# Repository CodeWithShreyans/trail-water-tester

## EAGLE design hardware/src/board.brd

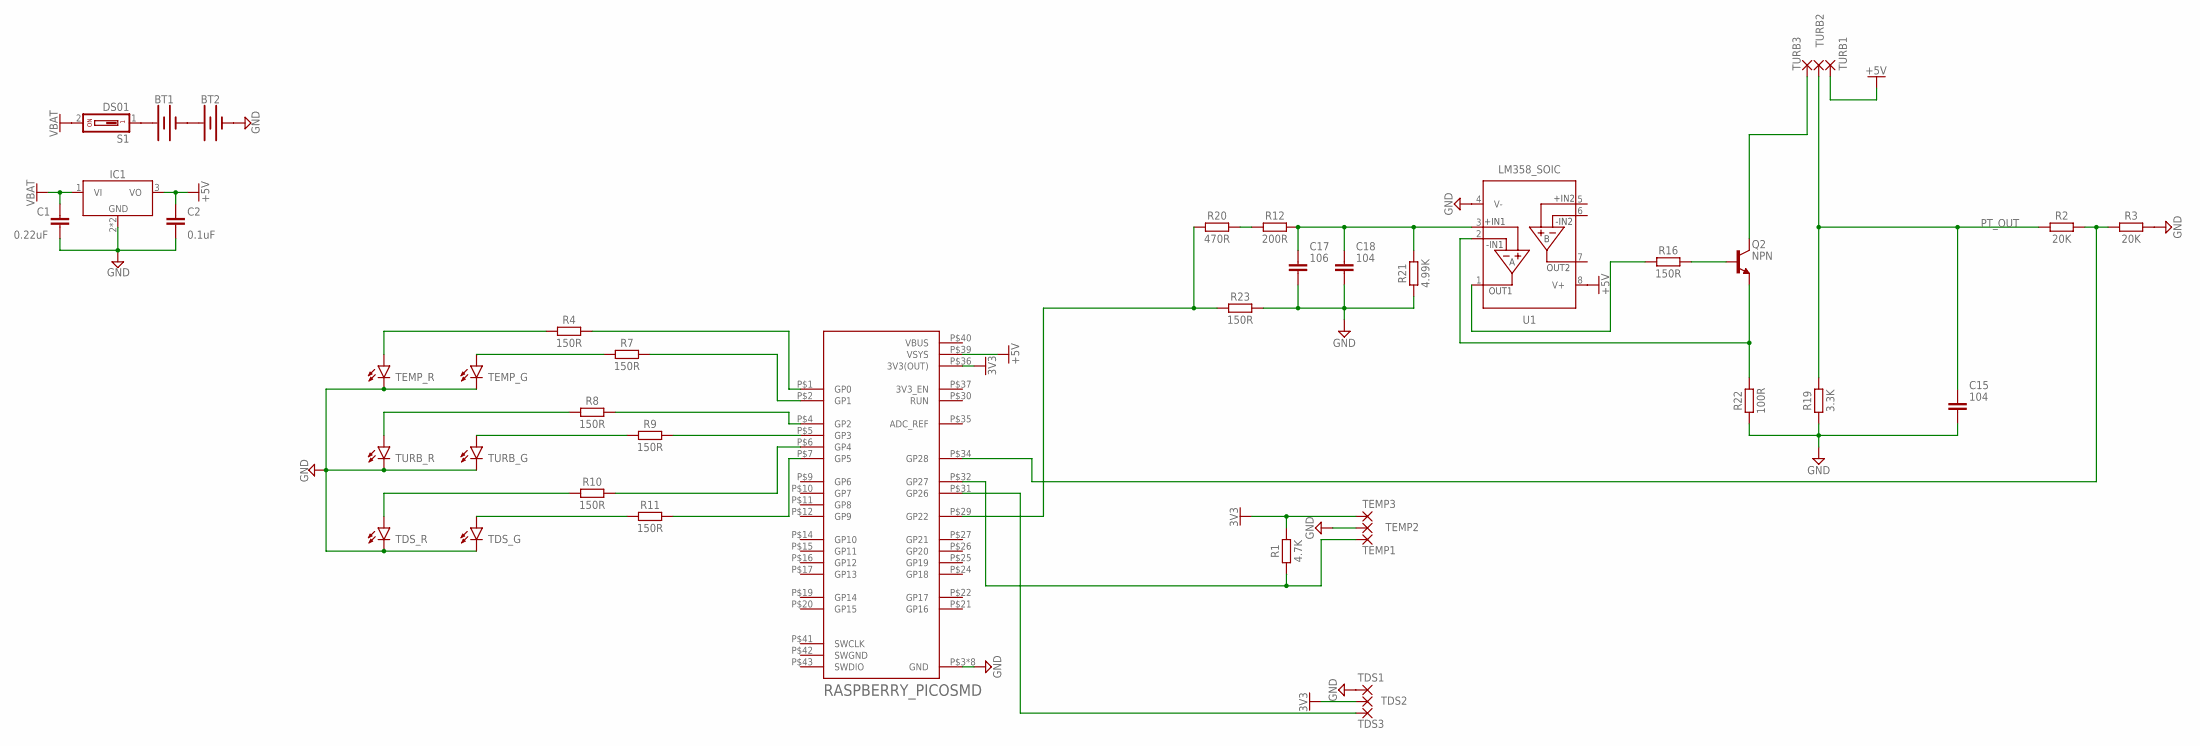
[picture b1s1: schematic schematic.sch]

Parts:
BT1, BT2: BATTERY-20MM_SMD_4LEGS; BATTCON_20MM_4LEGS
C1: 0.22uF; CAPC1608X85
C2: 0.1uF; CAPC1608X85
C15, C18: 104; CAPC1005X60
C17: 106; CAPC1005X60
IC1: LM7805_SOT223; SOT230P700X170-4
Q2: NPN; SOT95P237X112-3N
R1: 4.7K; RESC1005X40
R2, R3: 20K; RESC1005X40
R4, R7, R8, R9, R10, R11, R16, R23: 150R; RESC1005X40
R12: 200R; RESC1005X40
R19: 3.3K; RESC1005X40
R20: 470R; RESC1005X40
R21: 4.99K; RESC1608X60
R22: 100R; RESC1005X40
S1: DS01; DS-01
TDS1, TDS2, TDS3: SMD5; SMD2,54-5,08
TDS_G: CHIP-ROUND-G_0805; LEDC2012X105N_RND-G
TDS_R: CHIP-ROUND-R_0805; LEDC2012X105N_RND-R
TEMP1, TEMP2, TEMP3: SMD5; SMD2,54-5,08
TEMP_G: CHIP-ROUND-G_0805; LEDC2012X105N_RND-G
TEMP_R: CHIP-ROUND-R_0805; LEDC2012X105N_RND-R
TURB1, TURB2, TURB3: SMD5; SMD2,54-5,08
TURB_G: CHIP-ROUND-G_0805; LEDC2012X105N_RND-G
TURB_R: CHIP-ROUND-R_0805; LEDC2012X105N_RND-R
U1: LM358_SOIC; SOIC127P600X175-8N
U2: RASPBERRY_PICOSMD; PICO-PKG-SMD

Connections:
3V3: R1.2, TDS2.1, TEMP3.1, U2.P$36 (3V3(OUT))
+5V: C2.1, IC1.3 (VO), TURB1.1, U1.8 (V+), U2.P$39 (VSYS)
GND: BT2.NEGATIVE (-), C1.2, C2.2, C15.2, C17.2, C18.2, IC1.2 (GND), IC1.4 (GND), R3.2, R19.1, R21.1, R22.1, R23.2, TDS1.1, TDS_G.C, TDS_R.C, TEMP2.1, TEMP_G.C, TEMP_R.C, TURB_G.C, TURB_R.C, U1.4 (V-), U2.P$3 (GND), U2.P$8 (GND), U2.P$13 (GND), U2.P$18 (GND), U2.P$23 (GND), U2.P$28 (GND), U2.P$33 (GND), U2.P$38 (GND)
unnamed: R8.2, U2.P$4 (GP2)
unnamed: R9.2, U2.P$5 (GP3)
unnamed: R1.1, TEMP1.1, U2.P$32 (GP27)
unnamed: R20.1, R23.1, U2.P$29 (GP22)
unnamed: R2.2, R3.1, U2.P$34 (GP28)
unnamed: TDS3.1, U2.P$31 (GP26)
unnamed: R4.1, TEMP_R.A
unnamed: R7.1, TEMP_G.A
unnamed: R8.1, TURB_R.A
unnamed: R9.1, TURB_G.A
unnamed: R11.1, TDS_G.A
unnamed: BT1.NEGATIVE (-), BT2.POSITIVE@1 (+), BT2.POSITIVE@2 (+), BT2.POSITIVE@3 (+), BT2.POSITIVE@4 (+)
unnamed: R11.2, U2.P$7 (GP5)
unnamed: R10.2, U2.P$6 (GP4)
unnamed: BT1.POSITIVE@1 (+), BT1.POSITIVE@2 (+), BT1.POSITIVE@3 (+), BT1.POSITIVE@4 (+), S1.1
unnamed: R4.2, U2.P$1 (GP0)
unnamed: R7.2, U2.P$2 (GP1)
unnamed: R10.1, TDS_R.A
unnamed: R12.1, R20.2
unnamed: C17.1, C18.1, R12.2, R21.2, U1.3 (+IN1)
unnamed: R16.1, U1.1 (OUT1)
unnamed: Q2.1 (B), R16.2
unnamed: Q2.2 (E), R22.2, U1.2 (-IN1)
unnamed: Q2.3 (C), TURB3.1
PT_OUT: C15.1, R2.1, R19.2, TURB2.1
SWGND: U2.P$42 (SWGND)
VBAT: C1.1, IC1.1 (VI), S1.2
VBUS: U2.P$40 (VBUS)

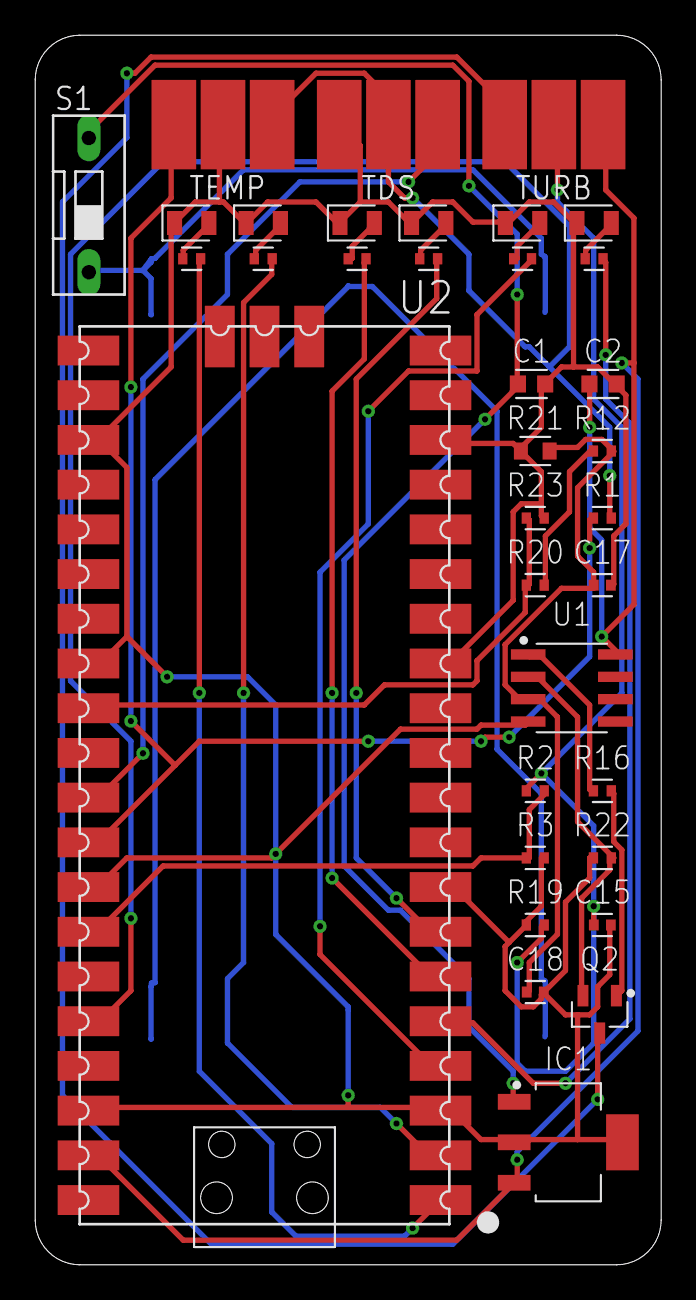
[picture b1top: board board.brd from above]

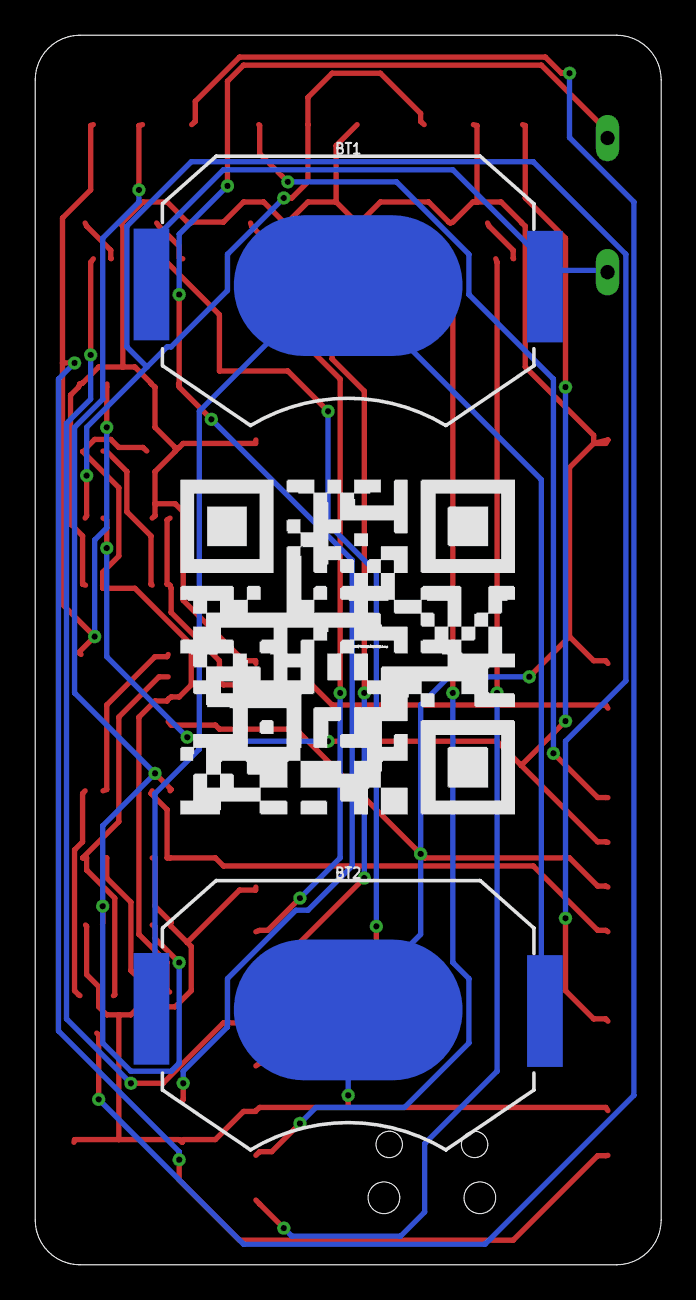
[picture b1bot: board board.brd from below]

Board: 2 copper layers, 35.6 x 69.8 mm, 43 parts (2 on the bottom side), 29 nets.

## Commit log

2024-06-26 add hardware files

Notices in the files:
parts and their libraries:
SparkFun-Batteries: Licensing: Creative Commons ShareAlike 4.0 International - https://creativecommons.org/licenses/by-sa/4.0
